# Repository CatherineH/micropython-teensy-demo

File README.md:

This repository contains electrical schematics and sample code to control a charlieplexed led matrix and some pushbutton switches using a teensy and micropython.

The parts in the electrical schematic are stored in [my eagle library repository](https://github.com/CatherineH/catherineh-eagle-libraries).

For more information on running the sample code, check out [my blog post on using micropython with the teensy](http://catherineh.github.io/programming/2016/09/18/getting-started-with-micropython-on-the-teensy).

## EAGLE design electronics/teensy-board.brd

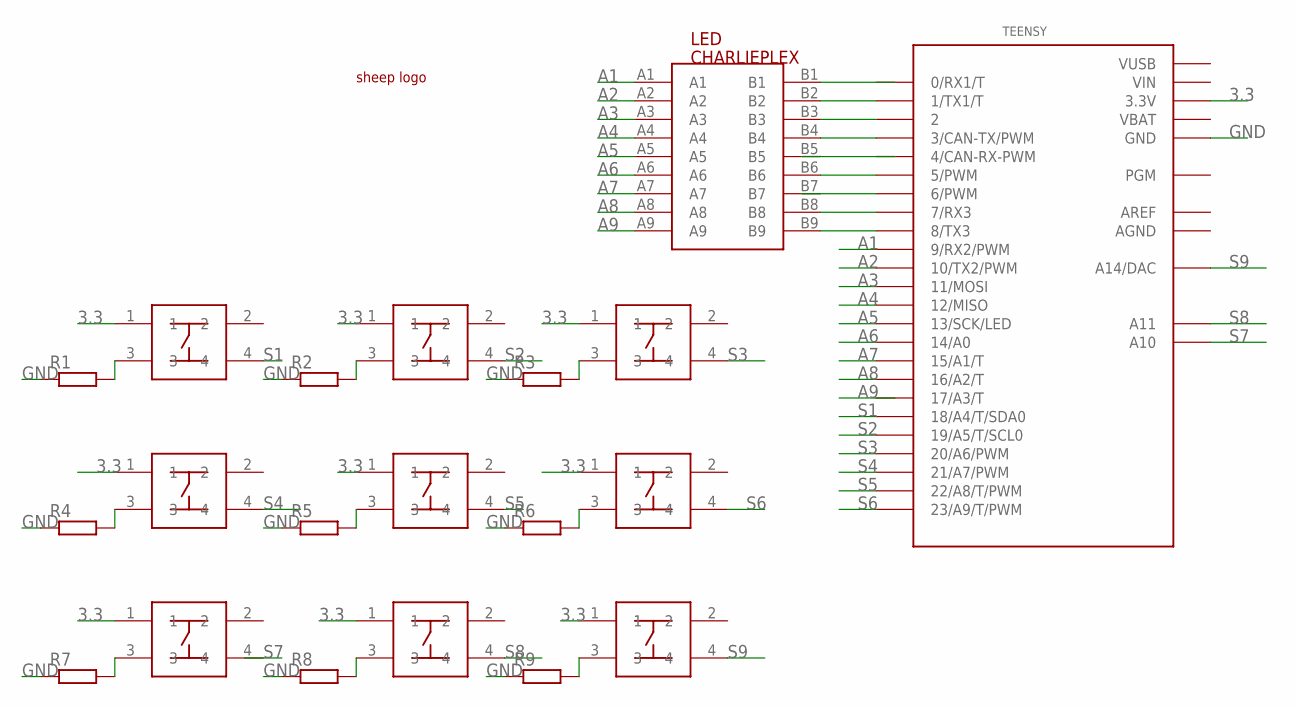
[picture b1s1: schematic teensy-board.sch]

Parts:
1, 2, 3, 4, 5, 6, 7, 8, 9: PUSHBUTTON
LED: CHARLIEPLEX; CHARLIEPLEXED
R1, R2, R3, R4, R5, R6, R7, R8, R9: R-EU_0207/10; 0207/10
TEENSY: TEENSY_3.1_ALL_PINS; TEENSY3-ALL_PINS
U$7: LOGO

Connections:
3.3: 1.1, 2.1, 3.1, 4.1, 5.1, 6.1, 7.1, 8.1, 9.1, TEENSY.3.3V, TEENSY.3.3V1 (3.3V)
A1: LED.A1, TEENSY.9 (9/RX2/PWM)
A2: LED.A2, TEENSY.10 (10/TX2/PWM)
A3: LED.A3, TEENSY.11 (11/MOSI)
A4: LED.A4, TEENSY.12 (12/MISO)
A5: LED.A5, TEENSY.13 (13/SCK/LED)
A6: LED.A6, TEENSY.14/A0
A7: LED.A7, TEENSY.15/A1 (15/A1/T)
A8: LED.A8, TEENSY.16/A2 (16/A2/T)
A9: LED.A9
AGND: TEENSY.AGND
AREF: TEENSY.AREF
GND: R1.1, R2.1, R3.1, R4.1, R5.1, R6.1, R7.1, R8.1, R9.1, TEENSY.GND, TEENSY.GND1 (GND)
unnamed: LED.B2, TEENSY.1 (1/TX1/T)
unnamed: LED.B3, TEENSY.2
unnamed: LED.B4, TEENSY.3 (3/CAN-TX/PWM)
unnamed: LED.B6, TEENSY.5 (5/PWM)
unnamed: LED.B8, TEENSY.7 (7/RX3)
unnamed: LED.B9, TEENSY.8 (8/TX3)
unnamed: 1.3, R1.2
unnamed: 2.3, R2.2
unnamed: 3.3, R3.2
unnamed: 4.3, R4.2
unnamed: 5.3, R5.2
unnamed: 6.3, R6.2
unnamed: 7.3, R7.2
unnamed: 8.3, R8.2
unnamed: 9.3, R9.2
S1: 1.4, TEENSY.18/A4 (18/A4/T/SDA0)
S2: 2.4, TEENSY.19/A5 (19/A5/T/SCL0)
S3: 3.4, TEENSY.20/A6 (20/A6/PWM)
S4: 4.4, TEENSY.21/A7 (21/A7/PWM)
S5: 5.4, TEENSY.22/A8 (22/A8/T/PWM)
S6: 6.4, TEENSY.23/A9 (23/A9/T/PWM)
S7: TEENSY.A10
S8: 8.4, TEENSY.A11
S9: 9.4, TEENSY.RESET/DAC (A14/DAC)
VBAT: TEENSY.VBAT
VIN: TEENSY.VIN
VUSB: TEENSY.VUSB

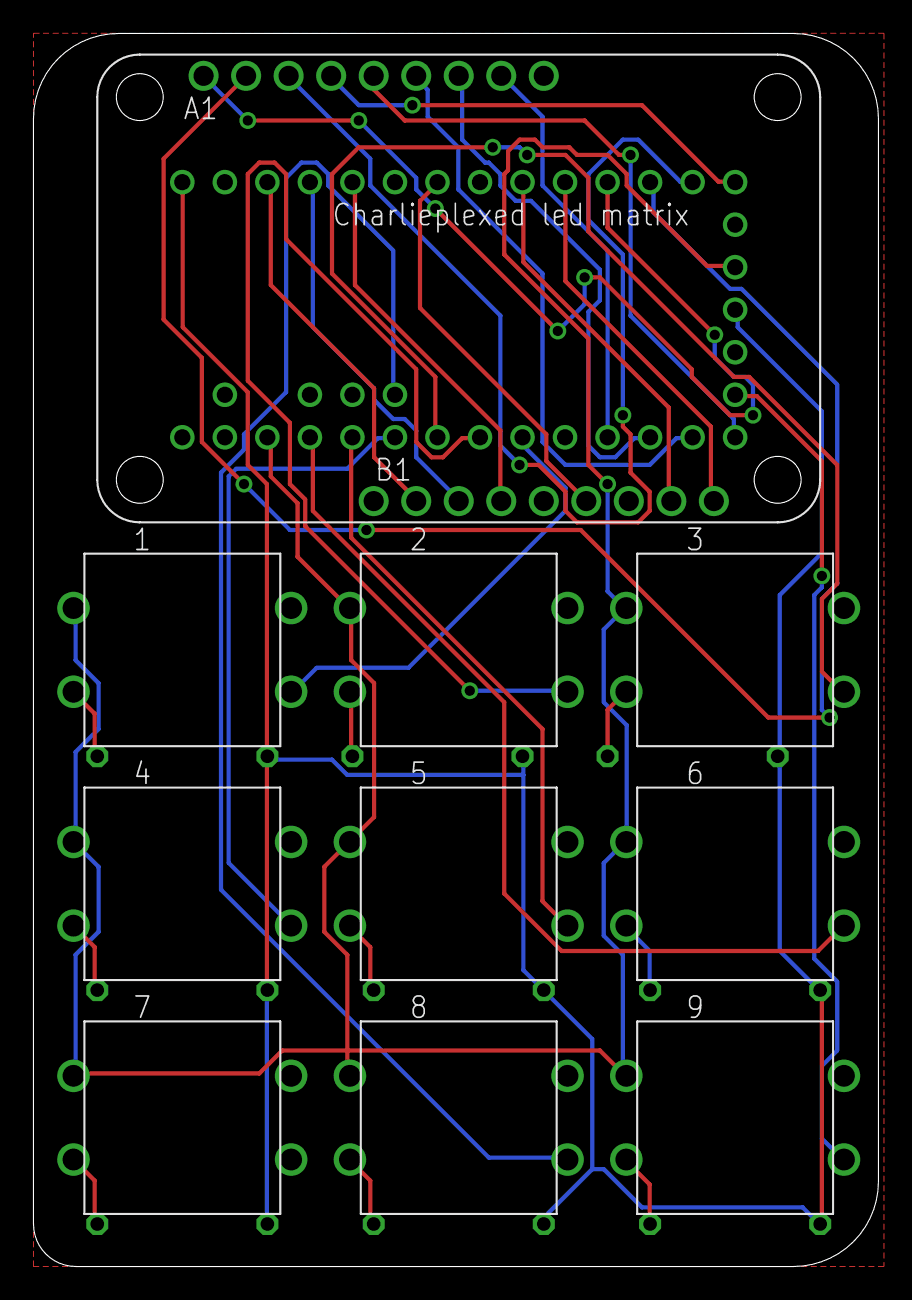
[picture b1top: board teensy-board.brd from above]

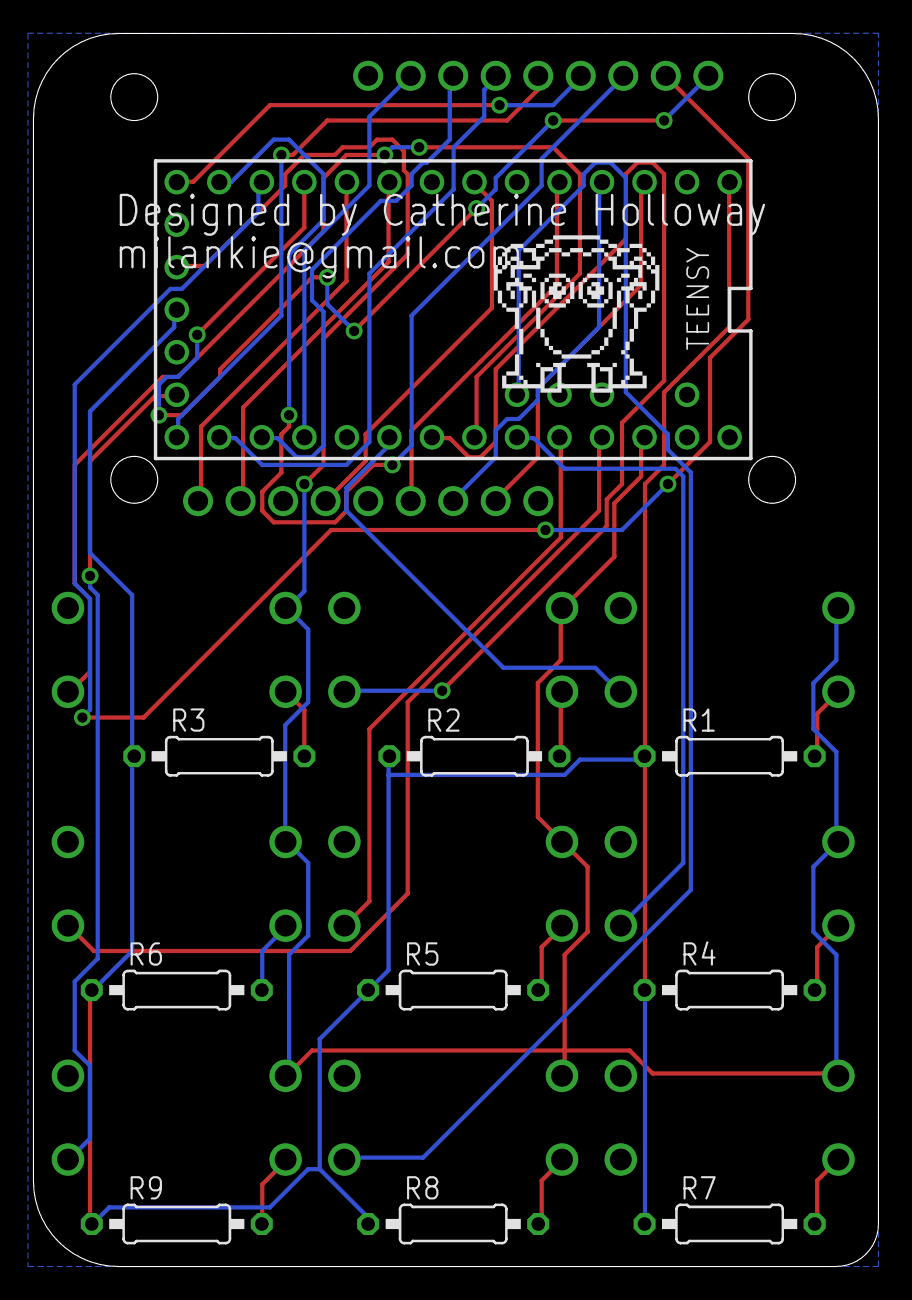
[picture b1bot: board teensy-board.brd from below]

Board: 2 copper layers, 50.5 x 73.7 mm, 21 parts (10 on the bottom side), 33 nets.

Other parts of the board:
E$1: LOGO

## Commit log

2016-09-11 added board files
2016-09-18 created main.py
2016-10-22 fixed flipped charlieplexed led
2016-10-24 adding pattern moving
2016-10-24 split display into two matrices
2016-10-26 add blink forever
2016-10-26 fixed bugs in show pattern
2016-10-27 re-enabling the move pattern
2016-10-27 added center button
2016-10-27 added a game
2016-10-27 remove pattern
